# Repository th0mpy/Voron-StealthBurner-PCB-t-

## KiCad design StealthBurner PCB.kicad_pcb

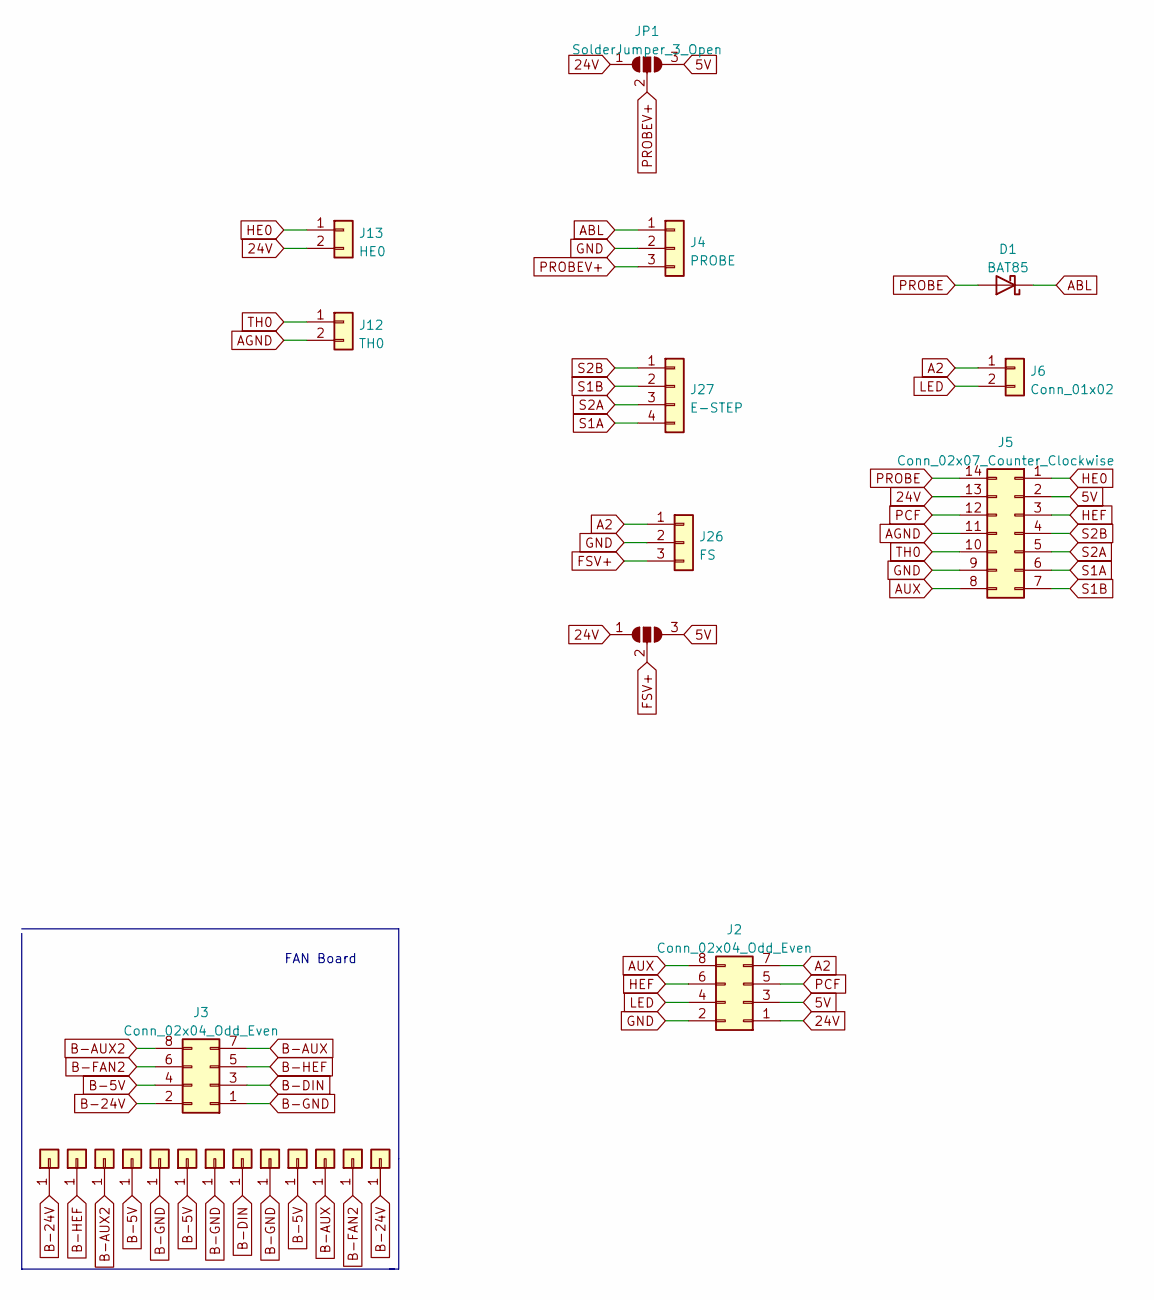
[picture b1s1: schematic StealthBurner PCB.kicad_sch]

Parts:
D1: BAT85; D_DO-35_SOD27_P7.62mm_Horizontal
J2, J3: Conn_02x04_Odd_Even; HDR-M-2.54_2X4
J4: PROBE; JST-PH-3P
J5: Conn_02x07_Counter_Clockwise; MICRO14
J6: Conn_01x02; Molex_Micro-Fit_3.0_43045-0200_2x01_P3.00mm_Horizontal
J12: TH0; 436500200_SB
J13: HE0; 436500200_SB
J26: FS; JST-PH-3P
J27: E-STEP; JST-PH-4P
J200, J201, J202, J203, J204, J205, J206, J207, J208, J209, J210, J211, J212: Conn_01x01; PinHeader_1x01_P1.00mm_Vertical_SMD
JP1, JP2: SolderJumper_3_Open; SolderJumper-3_P1.3mm_Open_RoundedPad1.0x1.5mm

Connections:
5V: J2.3, J5.2, JP1.3 (B), JP2.3 (B)
24V: J2.1, J5.13, J13.2, JP1.1 (A), JP2.1 (A)
A2: J2.7, J6.1, J26.1
ABL: D1.1 (K), J4.1
AGND: J5.11, J12.2
AUX: J2.8, J5.8
B-5V: J3.4, J203.1, J205.1, J209.1
B-24V: J3.2, J200.1, J212.1
B-AUX: J3.7, J210.1
B-AUX2: J3.8, J202.1
B-DIN: J3.3, J207.1
B-FAN2: J3.6, J211.1
B-GND: J3.1, J204.1, J206.1, J208.1
B-HEF: J3.5, J201.1
FSV+: J26.3, JP2.2 (C)
GND: J2.2, J4.2, J5.9, J26.2
HE0: J5.1, J13.1
HEF: J2.6, J5.3
LED: J2.4, J6.2
PCF: J2.5, J5.12
PROBE: D1.2 (A), J5.14
PROBEV+: J4.3, JP1.2 (C)
S1A: J5.6, J27.4
S1B: J5.7, J27.2
S2A: J5.5, J27.3
S2B: J5.4, J27.1
TH0: J5.10, J12.1

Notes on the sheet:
FAN Board

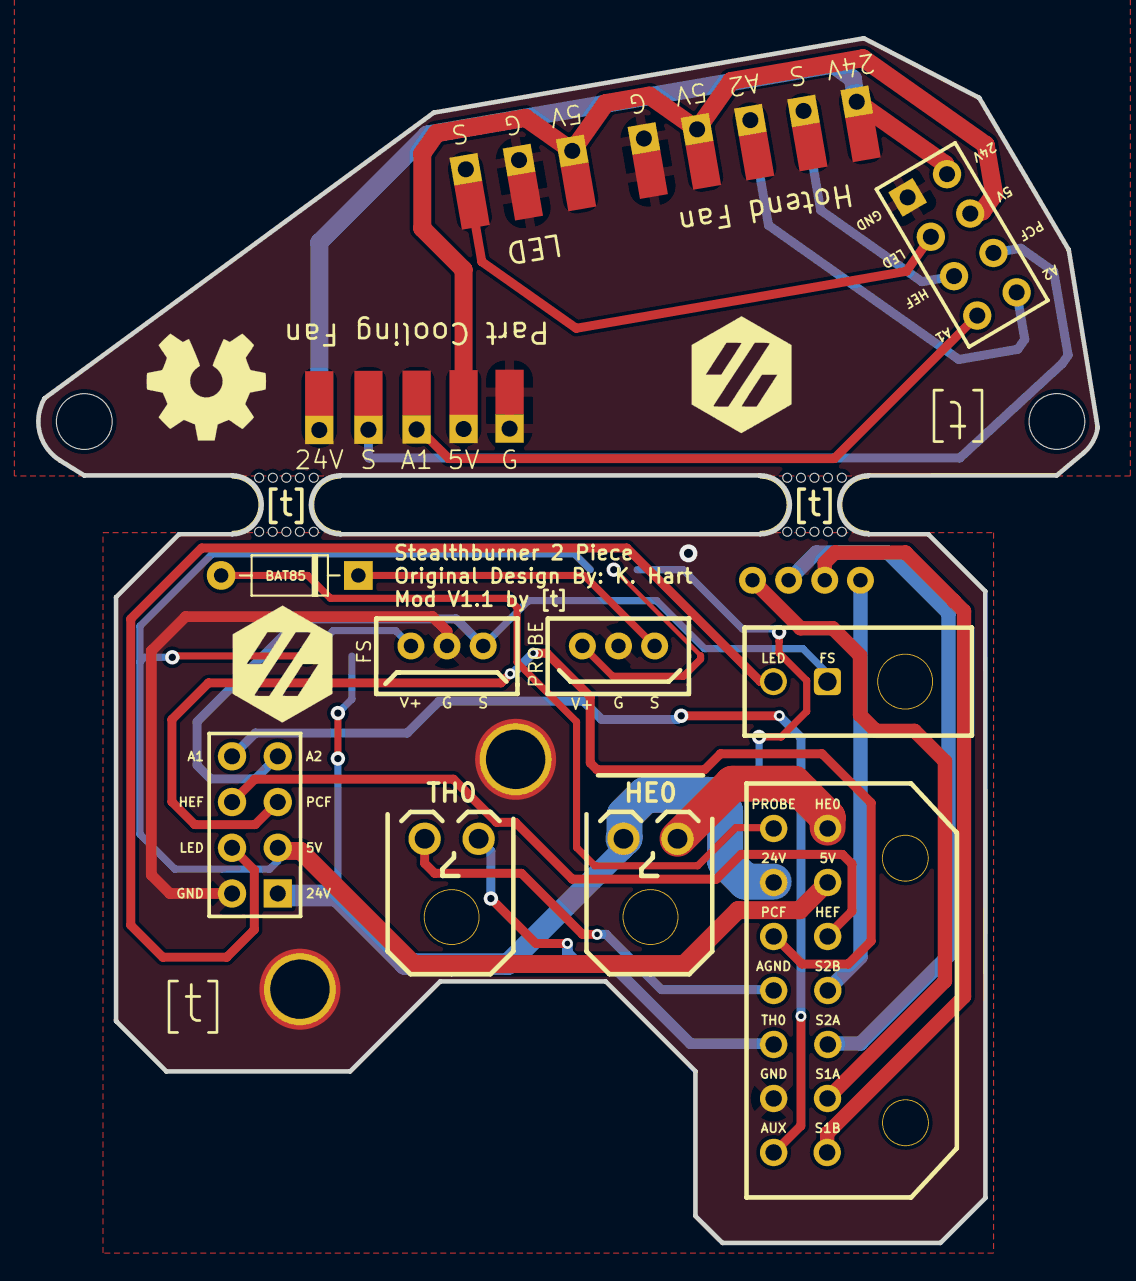
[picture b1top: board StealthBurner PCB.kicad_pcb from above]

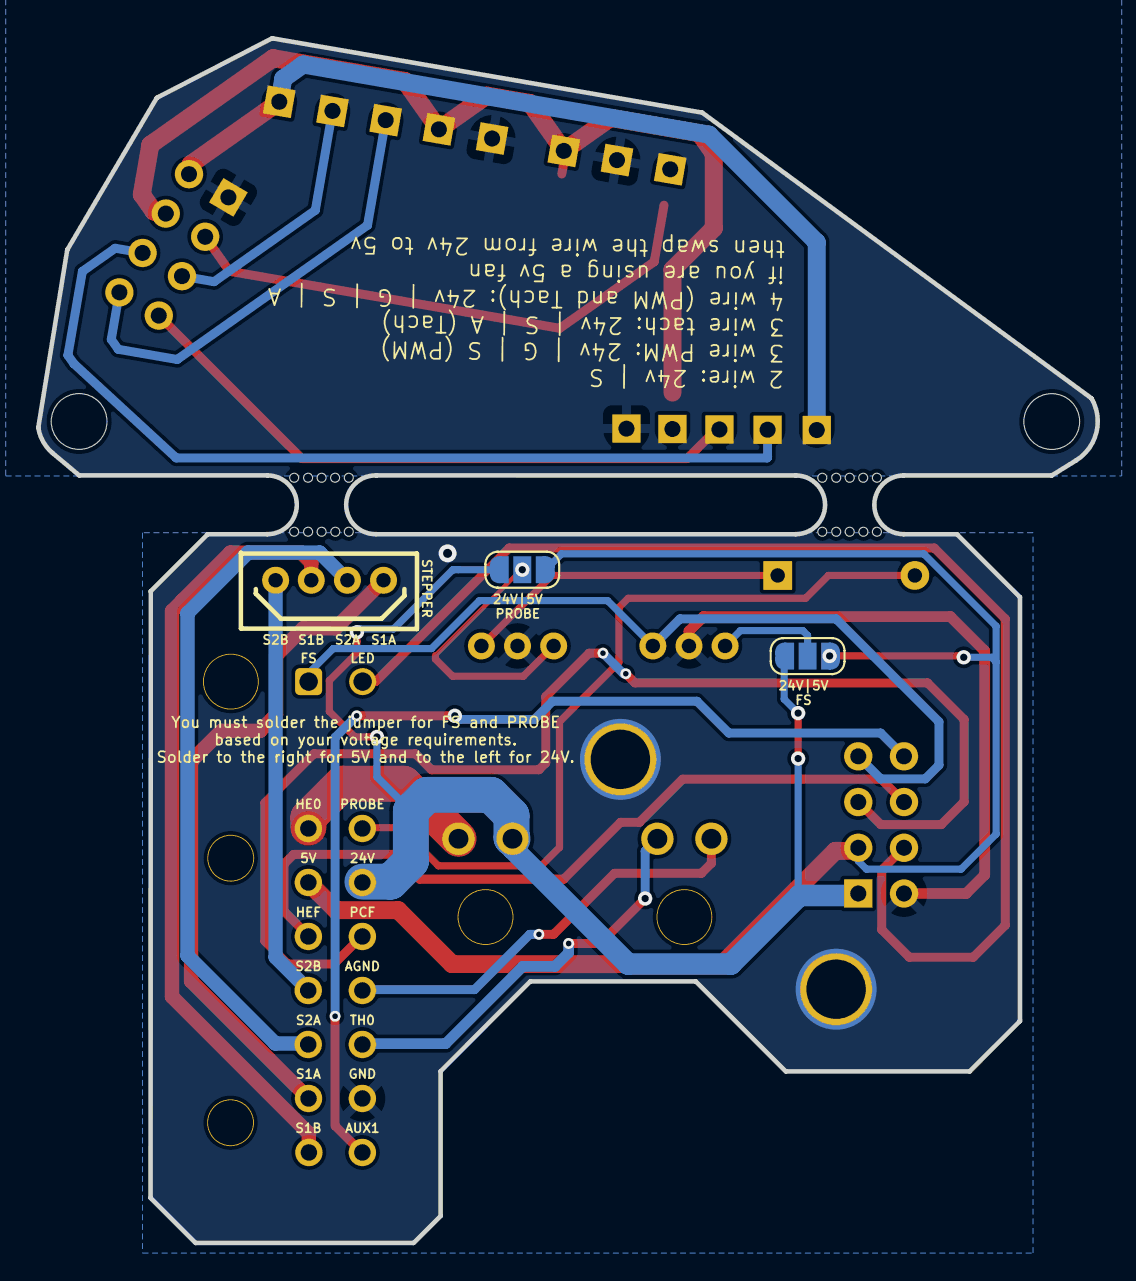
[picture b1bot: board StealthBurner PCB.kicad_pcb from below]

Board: 2 copper layers, 58.9 x 66.9 mm, 27 parts (2 on the bottom side), 27 nets.

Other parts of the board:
mouse-bite-3mm-slot, mouse-bite-3mm-slot#2: VAL**; mouse-bite-3mm-slot

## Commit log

2023-01-02 Initial upload
